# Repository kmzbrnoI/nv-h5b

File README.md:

NV-H5B
======

NV-H5B is a [S-COM](https://www.mtb-model.com/elektro/s-com.htm) receiver based
on [NV-7B](https://www.mtb-model.com/elektro/s-com-nav.htm). It is mounted
to the socket of a signal and displays signal code according to the received code
on data wire.

This repository contains KiCad schematics & pcb layout design as well as MCU
firmware source code.

## Basic features

 * 5 V power supply.
 * Mechanical compatibility with [NV-7D](https://www.mtb-model.com/elektro/s-com-nav.htm).
 * Receives [standard S-COM protocol](https://www.mtb-model.com/elektro/s-com.htm).
 * Separate resistor for each LED to unify brightness.
 * ATtiny25 main MCU.
 * Opensource & openhardware design.
 * [Supported signals (CZ)](signals.md).

## Recommended resistor values

### AŽD 70 signals by Josef Němeček

* Yellow: 4k7
* Red: 10k
* White: 22k
* Green: 2k2
* Blue: 22k

### AŽD 65 signals by Mr. Dvořáček (Pečky)

* Yellow: 1k
* Red: 10k
* White: 22k
* Green: 1k
* Blue: 47k

## Authors

 * [Jan Horacek](mailto:jan.horacek@kmz-brno.cz)

## License

PCBs are provided under [Creative Commons Attribution-ShareAlike 4.0
License](https://creativecommons.org/licenses/by-sa/4.0/) as openhardware
project. You may download any data, contribute to the project, create PCB
yourself or even sell it yourself.

Source code is provided under the [Apache License v2.0
](https://www.apache.org/licenses/LICENSE-2.0).

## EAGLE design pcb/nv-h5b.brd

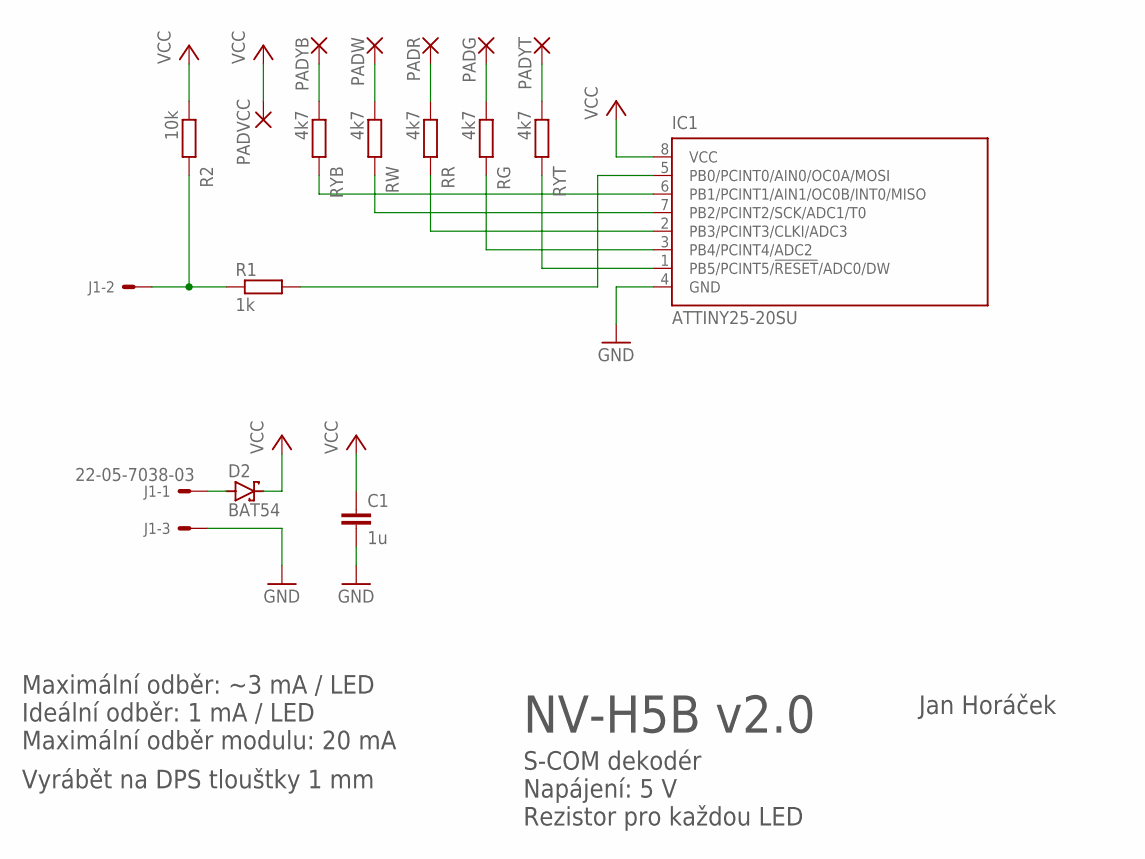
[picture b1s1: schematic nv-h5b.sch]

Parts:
C1: 1u; C0805
D2: BAT54; SOT23
IC1: ATTINY25-20SU; 8S1
J1: 22-05-7038-03; 7395-03
PADG: SMD3; SMD1,778-5,08
PADR: SMD3; SMD1,778-5,08
PADVCC: SMD3; SMD1,778-5,08
PADW: SMD3; SMD1,778-5,08
PADYB: SMD3; SMD1,778-5,08
PADYT: SMD3; SMD1,778-5,08
R1: 1k; R0805
R2: 10k; R0805
RG: 4k7; R0805
RR: 4k7; R0805
RW: 4k7; R0805
RYB: 4k7; R0805
RYT: 4k7; R0805

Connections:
DATAIN: J1.2, R1.1, R2.2
DATAIN_: IC1.5 (PB0/PCINT0/AIN0/OC0A/MOSI), R1.2
GND: C1.2, IC1.4 (GND), J1.3
GREEN: PADG.1, RG.1
unnamed: IC1.6 (PB1/PCINT1/AIN1/OC0B/INT0/MISO), RYB.2
unnamed: IC1.3 (PB4/PCINT4/ADC2), RG.2
unnamed: IC1.1 (PB5/PCINT5/!RESET!/ADC0/DW), RYT.2
unnamed: IC1.7 (PB2/PCINT2/SCK/ADC1/T0), RW.2
unnamed: IC1.2 (PB3/PCINT3/CLKI/ADC3), RR.2
RED: PADR.1, RR.1
VCC: C1.1, D2.3 (C), IC1.8 (VCC), PADVCC.1, R2.1
VIN: D2.1 (A), J1.1
WHITE: PADW.1, RW.1
YEL-BOT: PADYB.1, RYB.1
YEL-TOP: PADYT.1, RYT.1

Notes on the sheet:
Jan Horáček
NV-H5B v2.0
S-COM dekodér Napájení: 5 V Rezistor pro každou LED
Maximální odběr: ~3 mA / LED Ideální odběr: 1 mA / LED Maximální odběr modulu: 20 mA
Vyrábět na DPS tlouštky 1 mm

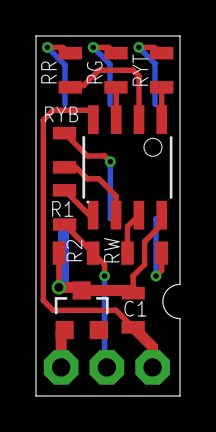
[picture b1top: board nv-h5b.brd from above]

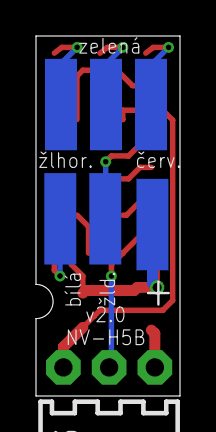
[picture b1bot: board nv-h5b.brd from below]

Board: 2 copper layers, 8.0 x 20.0 mm, 17 parts (7 on the bottom side), 15 nets.

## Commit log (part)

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2020-08-15 Add .gitignore.
2020-08-15 Initial version of schematics & PCB.
2020-08-15 Increase main capacitor.
2020-08-15 Increase LED resistors (~ max. 3 mA/ LED).
2020-08-15 Add info about power consumption.
2020-08-15 Use vector font for silkscreen.
2020-08-15 Move pcb layout to separate repository.
2020-08-15 PCB: add version.
2020-08-15 Add basic README.
2020-08-15 Add firmware template.
2020-08-15 fw: add leds basic functions.
2020-08-15 Add pwm module.
2020-08-15 Add test LED setting.
2020-08-15 Setup timer 0 @ 1 kHz.
2020-08-15 Balance PWM & timer frequency.
2020-08-15 Make PWM for all LEDs work.
2020-08-15 Add signal codes.
2020-08-15 Pwm: use #define to spare RAM.
2020-08-15 Make signal code setting work.
2020-08-15 Make flashing codes work.
2020-08-16 Use global counter & save RAM.
    Spare stack space when calling update.
2020-08-17 Add code receiving & upgrade CPU.
2020-08-17 Add codes for second signal type.
2020-08-17 Add signal type detection (untested).
2020-08-17 sch: use ATtiny25.
2020-08-17 Fix really silly bug.
2020-08-17 Add initial signal code setting.
2020-08-17 Add proper fuses & F_CPU to Makefile.
2020-08-17 Make S-COM code decoding work.
2020-08-17 Add double-check for code receiving.
2020-08-17 Do not show out-of-range codes.
2020-08-17 Switch MSB & LSB when receiving signal.
2020-08-18 Fix 0 code receiving.
2020-08-18 Tune PWM parameters for smaller period.
2020-08-18 Tweak flashing based on real signals videos.
2020-08-18 Do not interfere ramps.
2020-08-18 Fix flash code changes.
2020-08-18 Fix empty signal code.
2020-08-18 Remap LED for real MCU.
2020-08-21 Set LED properly when PWM rewrite.
2020-08-21 Move code to avoid race condition due to interrupt.
2020-08-21 Fix signal turnoff.
2020-08-21 Add missing turnof for blinking & !flash_state.
2020-08-21 Enable watchdog.
2020-09-22 Opravit orientaci vstupniho konektoru.
    Bylo opacne GND & VCC.
2020-09-22 Fix S-COM codes 9 & 10, add code 16.
2020-10-09 Make side drill smaller.
2021-03-20 Fix watchdog initialization.
2023-03-05 Move 'pcb' to 'old' directory (new PCB in KiCad).
2023-03-05 Update Eagle version.
2023-03-05 Add empty KiCad project.
2023-03-05 Finalize schematics.
2023-03-05 Route PCB.
2023-03-05 Silkscreen.
2023-03-05 Add panelization Makefile.
2023-03-05 kikit panelize: add tolerance.
2023-03-09 Add part names to silkscreen.
2023-03-09 Add *.kicad_prl to .gitignore.
2023-03-09 Create tester PCB: copy from NV-H5B pcb.
2023-03-09 Tester: add LEDs to chematics, route PCB.
2023-03-12 Use thin top width.
    Because signal must fit in tracks profile.
2023-03-15 NV-H5B tester -> NV-H5T.
2023-03-15 Add 3V3 stabilizer, so NV-H5T supports both 5V & 12V power supply.
2023-03-15 Make panel.
2023-03-19 Do not write eeprom.
2023-03-19 Note possible alterantive versions of MCU.
2023-03-21 Add AZD 70 resistor values.
2023-12-07 Remove silkscreen of main connector outside of PCB.
2023-12-20 Makefile: add minipro flashing.
2023-12-20 Add fuses.conf.
2023-12-26 Simplify Makefile.
2023-12-26 Move .c & . to 'src' dir.
2023-12-26 Simplify .gitignore.
2023-12-26 README: add links, enhance texts.
2024-07-04 Do not write flashing output to first item in record.
2024-07-04 Delay turning the red LED off.
    In reality, the red light is turned off only after a successful validation
    of the allowing aspect.
2024-07-05 Always reset signal counter.
    Avoid the need for relationship with 65536.
2024-07-05 Save space by changing type to uint8_t.
2024-07-05 Use enum for signal type.
2024-07-05 Use void where appropriate.
2024-07-05 Add initial led test.
2024-07-06 Receive code during init test.
    If valid code is already received at the end of the initial test,
    show directly the code.
2024-07-07 Decrease red LED turnoff delay to 150 ms.
    This a more realisitc behavior.
    Previous value: ~800 ms.
2024-07-07 Place firmware name & version at the end of flash.
2024-07-20 README: add AZD 65 recommended resistor values.
2024-08-03 Use new fuses.conf format (minipro v0.7).
2024-08-03 README: update AZD 65 recommended resistors.
2024-08-06 Better S-COM variant detection.
2024-08-09 AZD65: add recommended blue resistor.
2024-12-04 README: add blue LED resistor value (22k).
2025-05-02 Prolong red-turnoff-delay to 550 ms.
    Recorded in real world: 630 ms.
2025-06-19 Add table of supported signals.
2025-06-19 Signals: full text, add first extension.
2025-06-19 signals.md: add more explanation.
2025-06-19 Add more new signals.
2025-06-19 Signals: add repeating signals for higher speeds.
2025-06-20 signal: add speed indicators.
2025-06-20 signals.md: add lights & expected codes.
2025-06-20 signals.md: add note regarding RIA & RIB general outputs.
2025-06-20 signals.md: add examples, add notes.
2025-06-21 signals.md: fix flicker frequency.
2025-06-22 signals.md: add open points.
2025-07-20 Disable spare peripherals to reduce power consumption.
